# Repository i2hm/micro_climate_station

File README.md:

# Micro Climate Station

PCB designs and firmwares for the Microclimate station.

* [Microclimate station board based on LoRa RAK3172 module](kicad/rak3172_board)
* [Microclimate station board extension for MPPT and PMS7003](kicad/mppt_pms7003_board)
* [868 MHz PCB antenna for LoRa RAK3172 module](kicad/antenna_eu868)
* [Mikrobus adapter for Quectel RTK GNSS LC29H module](kicad/lc29h_mikrobus)

## Licence

[CERN Open Hardware Licence Version 2 - Strongly Reciprocal](./LICENCE.txt) ([wiki](https://ohwr.org/project/cernohl/wikis/home))

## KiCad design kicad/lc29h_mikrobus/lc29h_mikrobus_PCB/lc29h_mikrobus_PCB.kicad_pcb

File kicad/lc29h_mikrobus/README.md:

# Mikrobus click for Quectel LC29H GNSS RTK modules

Designed by Jihane ZEMMOURA with [KiCad EDA](https://www.kicad.org/)

This Mikrobus module is a simplified variant to the [GNSS RTK 3 Click (MIKROE-5914)](https://www.mikroe.com/gnss-rtk-3-click) ([schematic](../../doc/gnss_rtk_3_click/GNSS_RTK_3_Click_v100_Schematic.PDF)).

Its design respects the [Mikrobus form factor](https://download.mikroe.com/documents/standards/mikrobus/mikrobus-standard-specification-v200.pdf). But it is only for 3.3V MCU (ie there is no [voltage regulator](https://product.torexsemi.com/en/system/files/series/xc6209.pdf)). LED are enabled by zero ohm resistors for low-power considerations. The identifier crypto chip ([DS28E36BQ](https://www.maximintegrated.com/en/products/embedded-security/secure-authenticators/DS28C36.html/storefront/my-quotes.html)) is optional.

Thanks to Quectel for supporting us:
* 17 [LC29HEAMD](https://www.quectel.com/product/gnss-lc29h) for rovers
* 8 [LC29HBSAMD](https://www.quectel.com/product/gnss-lc29h) for bases
* 25 [YG0063AA L1/L2/L5 high precision GNSS antennas](https://www.quectel.com/product/yg0063aa-high-precision-gnss-screw-mount-antenna/) + 3m cable TNC-K (F) to SMA(M) , RG174 cable

[Schematic](schematic.pdf)

Configuration tool QGNSS :
* https://market.quectel.com/docsdownload/QGNSS_V1.10_EN.zip
* https://github.com/quectel-open-source/GNSSTool

[Manuals and documents](../../doc/quectel)

## Misc
* [LC29H @ rtklibexplorer](https://rtklibexplorer.wordpress.com/?s=LC29H)
* [TinyGS 2G4 : LoRa 2.4 GHz + GNSS RTK](https://github.com/thingsat/tinygs_2g4station)
* [Integration of LoRa technology and centimeter-level geo-localization by satellites in GNSS/RTK systems](https://journees-lpwan-2023.liglab.fr/Presentations/poster-RTK-LoRa.pdf) (N. Palix, Univ. Grenoble Alpes)
* [LC29H hat for RPI](https://www.waveshare.com/wiki/LC29H(XX)_GPS/RTK_HAT)
* [Pi Click Shield MIKROE-1513](https://www.mikroe.com/pi-click-shield-connectors-soldered) for Raspberry Pi

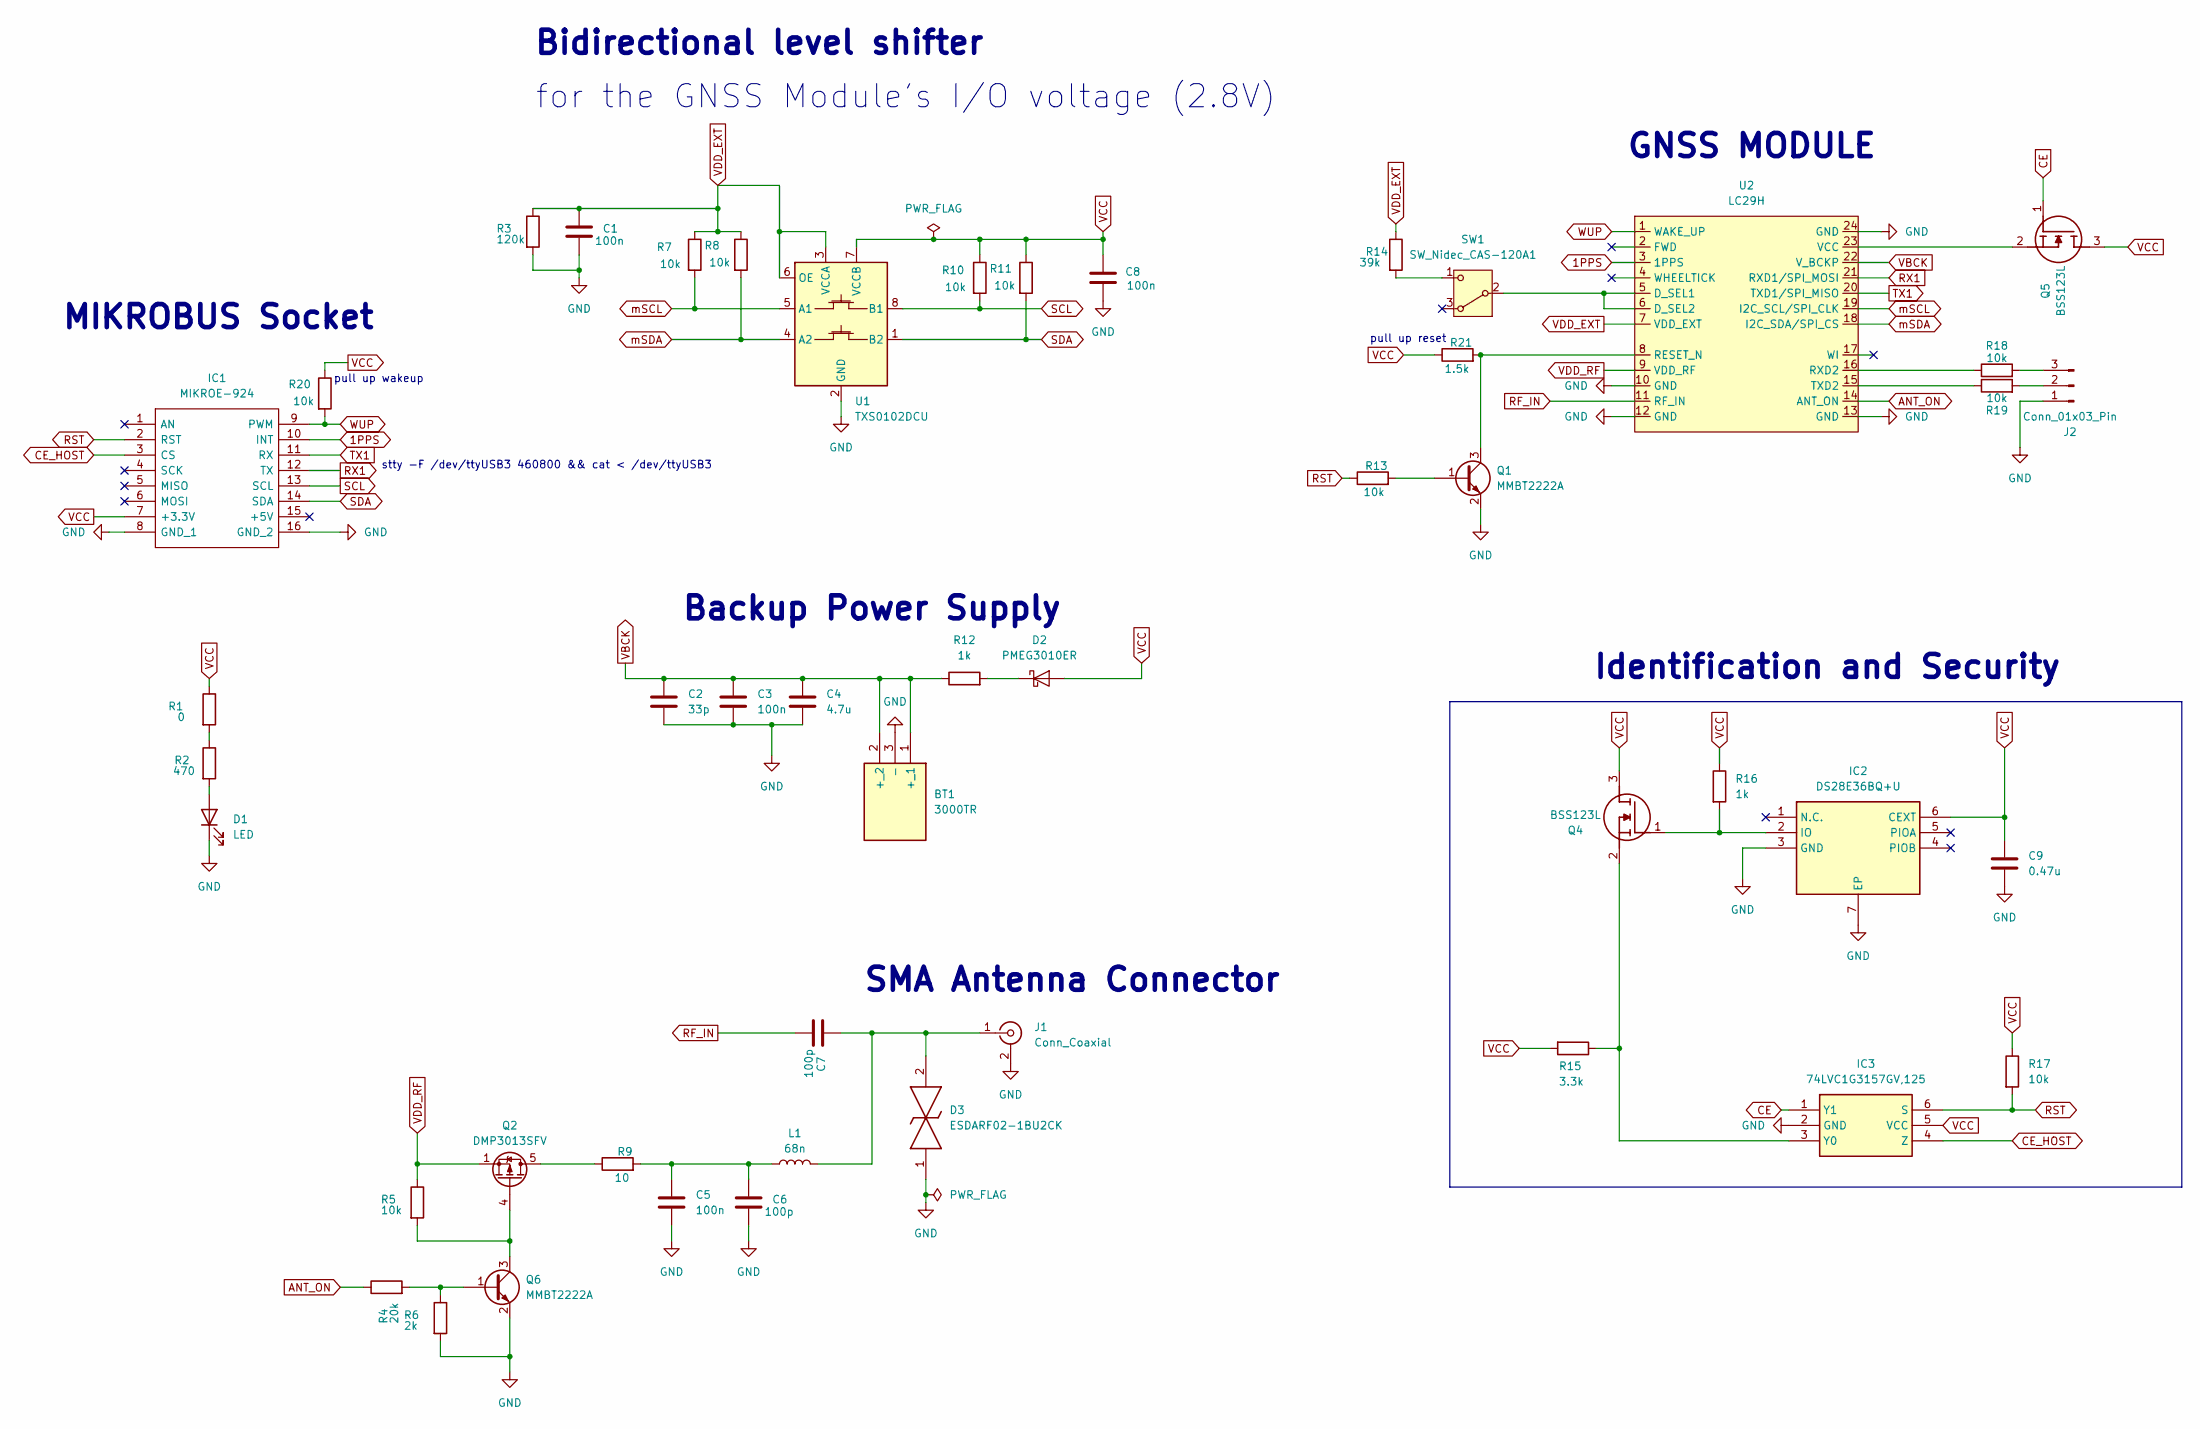
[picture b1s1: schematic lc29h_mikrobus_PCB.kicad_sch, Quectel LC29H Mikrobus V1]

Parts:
BT1: 3000TR; Manufacturer_Part_Number 3000TR; Mouser Part Number 534-3000TR
C1, C3, C5, C8: 100n; C_0805_2012Metric_Pad1.18x1.45mm_HandSolder
C2: 33p; C_0805_2012Metric_Pad1.18x1.45mm_HandSolder
C4: 4.7u; C_0805_2012Metric_Pad1.18x1.45mm_HandSolder
C6, C7: 100p; C_0805_2012Metric_Pad1.18x1.45mm_HandSolder
C9: 0.47u; C_0805_2012Metric_Pad1.18x1.45mm_HandSolder
D1: LED; LED_0402_1005Metric
D2: PMEG3010ER; Nexperia_CFP3_SOD-123W
D3: ESDARF02-1BU2CK; ESDARF021BU2CK; Manufacturer_Part_Number ESDARF02-1BU2CK; Mouser Part Number 511-ESDARF02-1BU2CK
IC1: MIKROE-924; MIKROE924; Manufacturer_Part_Number MIKROE-924; Mouser Part Number 932-MIKROE-924
IC2: DS28E36BQ+U; SON95P300X300X80-7N; Manufacturer_Part_Number DS28E36BQ+U; Mouser Part Number 700-DS28E36BQ+U
IC3: 74LVC1G3157GV,125; SOP95P275X110-6N; Manufacturer_Part_Number 74LVC1G3157GV,125
J1: Conn_Coaxial; SMA_Amphenol_901-144_Vertical
J2: Conn_01x03_Pin; PinHeader_1x03_P1.27mm_Vertical
L1: 68n; L_0805_2012Metric_Pad1.05x1.20mm_HandSolder
Q1, Q6: MMBT2222A; SOT-23
Q2: DMP3013SFV; Diodes_PowerDI3333-8
Q4, Q5: BSS123L; SOT96P237X111-3N; Manufacturer_Part_Number BSS123L; Mouser Part Number 512-BSS123L
R1: 0; R_0603_1608Metric_Pad0.98x0.95mm_HandSolder
R2: 470; R_0805_2012Metric_Pad1.20x1.40mm_HandSolder
R3: 120k; R_0805_2012Metric_Pad1.20x1.40mm_HandSolder
R4: 20k; R_0805_2012Metric_Pad1.20x1.40mm_HandSolder
R5, R7, R8, R10, R11, R13, R17, R18, R19, R20: 10k; R_0805_2012Metric_Pad1.20x1.40mm_HandSolder
R6: 2k; R_0805_2012Metric_Pad1.20x1.40mm_HandSolder
R9: 10; R_0805_2012Metric_Pad1.20x1.40mm_HandSolder
R12, R16: 1k; R_0805_2012Metric_Pad1.20x1.40mm_HandSolder
R14: 39k; R_0805_2012Metric_Pad1.20x1.40mm_HandSolder
R15: 3.3k; R_0805_2012Metric_Pad1.20x1.40mm_HandSolder
R21: 1.5k; R_0805_2012Metric_Pad1.20x1.40mm_HandSolder
SW1: SW_Nidec_CAS-120A1; Nidec_Copal_CAS-120A
U1: TXS0102DCU; VSSOP-8_2.3x2mm_P0.5mm
U2: LC29H; LC29HEA

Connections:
1PPS: IC1.10 (INT), U2.3 (1PPS)
ANT_ON: R4.1, U2.14 (ANT_ON)
CE: IC3.1 (Y1), Q5.1 (G)
CE_HOST: IC1.3 (CS), IC3.4 (Z)
GND: BT1.3 (-), C1.2, C2.2, C3.2, C4.2, C5.2, C6.2, C8.2, C9.2, D1.1 (K), D3.1, IC1.8 (GND_1), IC1.16 (GND_2), IC2.3 (GND), IC2.7 (EP), IC3.2 (GND), J1.2 (Ext), J2.1, Q1.2 (E), Q6.2 (E), R3.2, R6.2, U1.2 (GND), U2.10 (GND), U2.12 (GND), U2.13 (GND), U2.24 (GND)
unnamed: C5.1, C6.1, L1.1, R9.2
unnamed: D1.2 (A), R2.2
unnamed: D2.1 (K), R12.2
unnamed: IC2.2 (IO), Q4.1 (G), R16.2
unnamed: IC3.3 (Y0), Q4.2 (S), R15.1
unnamed: C7.1, D3.2, J1.1 (In), L1.2
unnamed: J2.2, R19.2
unnamed: J2.3, R18.2
unnamed: Q1.1 (B), R13.2
unnamed: Q1.3 (C), R21.2, U2.8 (RESET_N)
unnamed: Q2.5 (D), R9.1
unnamed: Q2.4 (G), Q6.3 (C), R5.2
unnamed: Q5.2 (S), U2.23 (VCC)
unnamed: Q6.1 (B), R4.2, R6.1
unnamed: R1.2, R2.1
unnamed: SW1.2 (B), U2.5 (D_SEL1), U2.6 (D_SEL2)
unnamed: R14.2, SW1.1 (C)
unnamed: R18.1, U2.16 (RXD2)
unnamed: R19.1, U2.15 (TXD2)
RF_IN: C7.2, U2.11 (RF_IN)
RST: IC1.2 (RST), IC3.6 (S), R13.1, R17.2
RX1: IC1.12 (TX), U2.21 (RXD1/SPI_MOSI)
SCL: IC1.13 (SCL), R10.2, U1.8 (B1)
SDA: IC1.14 (SDA), R11.2, U1.1 (B2)
TX1: IC1.11 (RX), U2.20 (TXD1/SPI_MISO)
VBCK: BT1.1 (+_1), BT1.2 (+_2), C2.1, C3.1, C4.1, R12.1, U2.22 (V_BCKP)
VCC: C8.1, C9.1, D2.2 (A), IC1.7 (+3.3V), IC2.6 (CEXT), IC3.5 (VCC), Q4.3 (D), Q5.3 (D), R1.1, R10.1, R11.1, R15.2, R16.1, R17.1, R20.1, R21.1, U1.7 (VCCB)
VDD_EXT: C1.1, R3.1, R7.1, R8.1, R14.1, U1.3 (VCCA), U1.6 (OE), U2.7 (VDD_EXT)
VDD_RF: Q2.1 (S), Q2.2 (S), Q2.3 (S), R5.1, U2.9 (VDD_RF)
WUP: IC1.9 (PWM), R20.2, U2.1 (WAKE_UP)
mSCL: R7.2, U1.5 (A1), U2.19 (I2C_SCL/SPI_CLK)
mSDA: R8.2, U1.4 (A2), U2.18 (I2C_SDA/SPI_CS)

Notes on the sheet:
Identification and Security
Backup Power Supply
SMA Antenna Connector
pull up reset
stty -F /dev/ttyUSB3 460800 && cat < /dev/ttyUSB3
MIKROBUS Socket
GNSS MODULE
Bidirectional level shifter
for the GNSS Module's I/O voltage (2.8V)
pull up wakeup

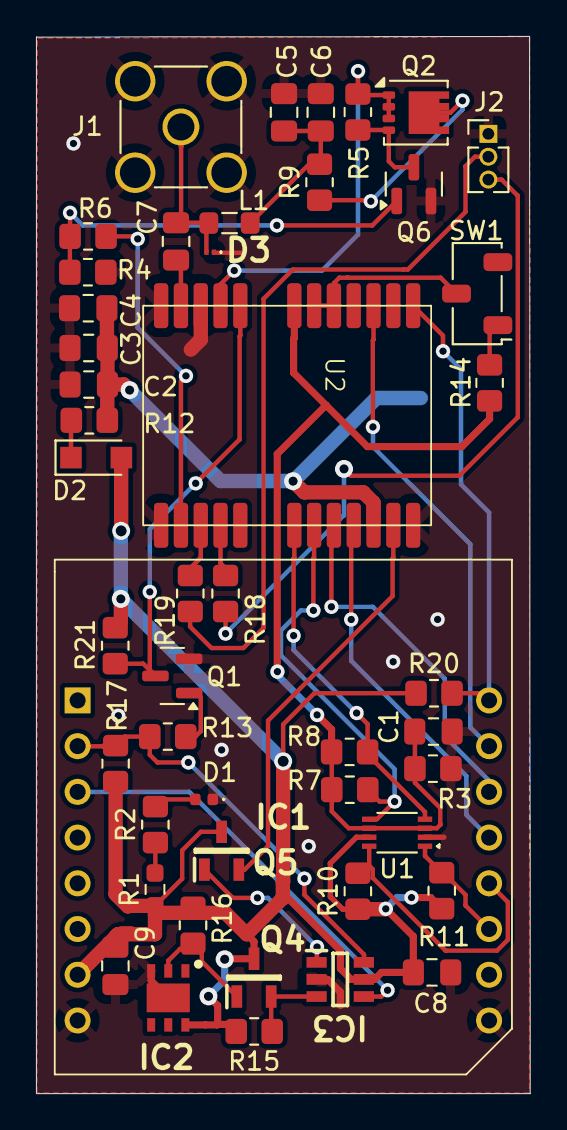
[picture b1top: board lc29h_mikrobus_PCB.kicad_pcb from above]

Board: 2 copper layers, 27.4 x 58.7 mm, 48 parts (1 on the bottom side), 37 nets.

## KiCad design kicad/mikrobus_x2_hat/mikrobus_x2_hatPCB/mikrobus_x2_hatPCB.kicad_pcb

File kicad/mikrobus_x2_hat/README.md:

# Two-slots Mikrobus hat for Raspberry Pi

This hat enables the connection of two Mikrobus click boards to the RPI GPIO header.

## Tested
* [x] [MIKROE-4456 GNSS RTK Click](https://www.mikroe.com/gnss-rtk-click)

## TODO
* [x] fix serigraphy for GPIOs
* [ ] add label and RPI logo in serigraphy
* [ ] add 4 Grove connectors for 1 UART, 1 GPIO and 2 I2C
* [ ] add selector for 3V3 or 5V0 on Grove connectors

## Misc
* https://github.com/devbisme/RPi_Hat_Template
* https://www.mikroe.com/pi-3-click-shield
* https://www.mikroe.com/pi-2-click-shield

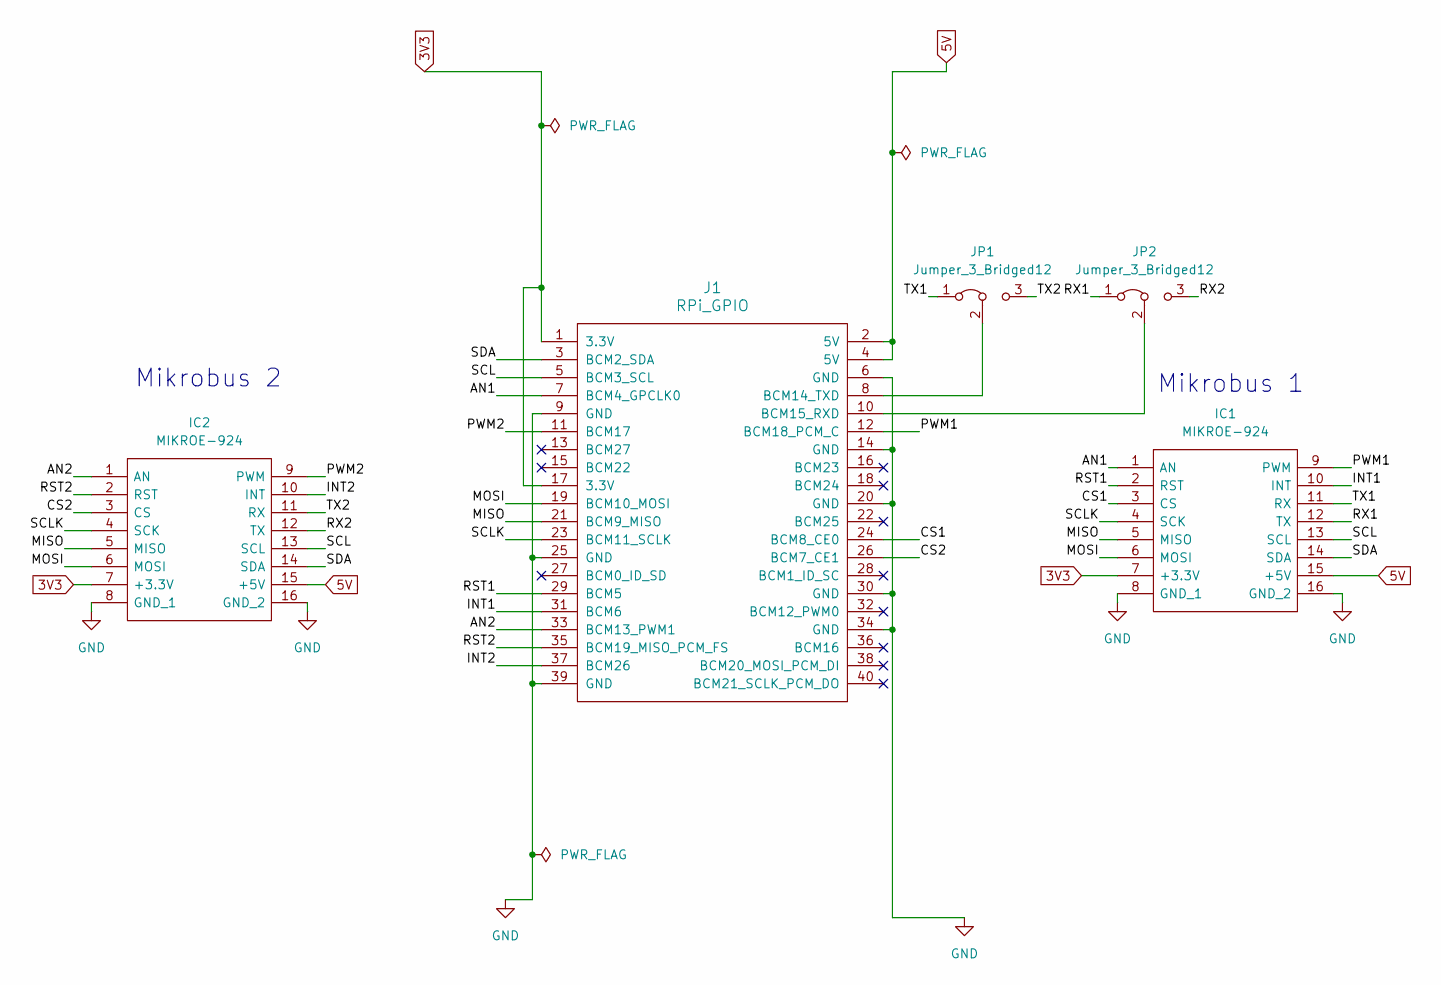
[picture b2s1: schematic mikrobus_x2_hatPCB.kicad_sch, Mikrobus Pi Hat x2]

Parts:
IC1, IC2: MIKROE-924; MIKROE924; Manufacturer_Part_Number MIKROE-924; Mouser Part Number 932-MIKROE-924
J1: RPi_GPIO; PinSocket_2x20_P2.54mm_Vertical
JP1, JP2: Jumper_3_Bridged12; PinHeader_1x03_P2.54mm_Vertical

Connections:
3V3: IC1.7 (+3.3V), IC2.7 (+3.3V), J1.1 (3.3V), J1.17 (3.3V)
5V: IC1.15 (+5V), IC2.15 (+5V), J1.2 (5V), J1.4 (5V)
/AN1: IC1.1 (AN), J1.7 (BCM4_GPCLK0)
/AN2: IC2.1 (AN), J1.33 (BCM13_PWM1)
/CS1: IC1.3 (CS), J1.24 (BCM8_CE0)
/CS2: IC2.3 (CS), J1.26 (BCM7_CE1)
/INT1: IC1.10 (INT), J1.31 (BCM6)
/INT2: IC2.10 (INT), J1.37 (BCM26)
/MISO: IC1.5 (MISO), IC2.5 (MISO), J1.21 (BCM9_MISO)
/MOSI: IC1.6 (MOSI), IC2.6 (MOSI), J1.19 (BCM10_MOSI)
/PWM1: IC1.9 (PWM), J1.12 (BCM18_PCM_C)
/PWM2: IC2.9 (PWM), J1.11 (BCM17)
/RST1: IC1.2 (RST), J1.29 (BCM5)
/RST2: IC2.2 (RST), J1.35 (BCM19_MISO_PCM_FS)
/RX1: IC1.12 (TX), JP2.1 (A)
/RX2: IC2.12 (TX), JP2.3 (B)
/SCL: IC1.13 (SCL), IC2.13 (SCL), J1.5 (BCM3_SCL)
/SCLK: IC1.4 (SCK), IC2.4 (SCK), J1.23 (BCM11_SCLK)
/SDA: IC1.14 (SDA), IC2.14 (SDA), J1.3 (BCM2_SDA)
/TX1: IC1.11 (RX), JP1.1 (A)
/TX2: IC2.11 (RX), JP1.3 (B)
GND: IC1.8 (GND_1), IC1.16 (GND_2), IC2.8 (GND_1), IC2.16 (GND_2), J1.6 (GND), J1.9 (GND), J1.14 (GND), J1.20 (GND), J1.25 (GND), J1.30 (GND), J1.34 (GND), J1.39 (GND)
unnamed: J1.8 (BCM14_TXD), JP1.2 (C)
unnamed: J1.10 (BCM15_RXD), JP2.2 (C)

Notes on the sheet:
Mikrobus 2
Mikrobus 1

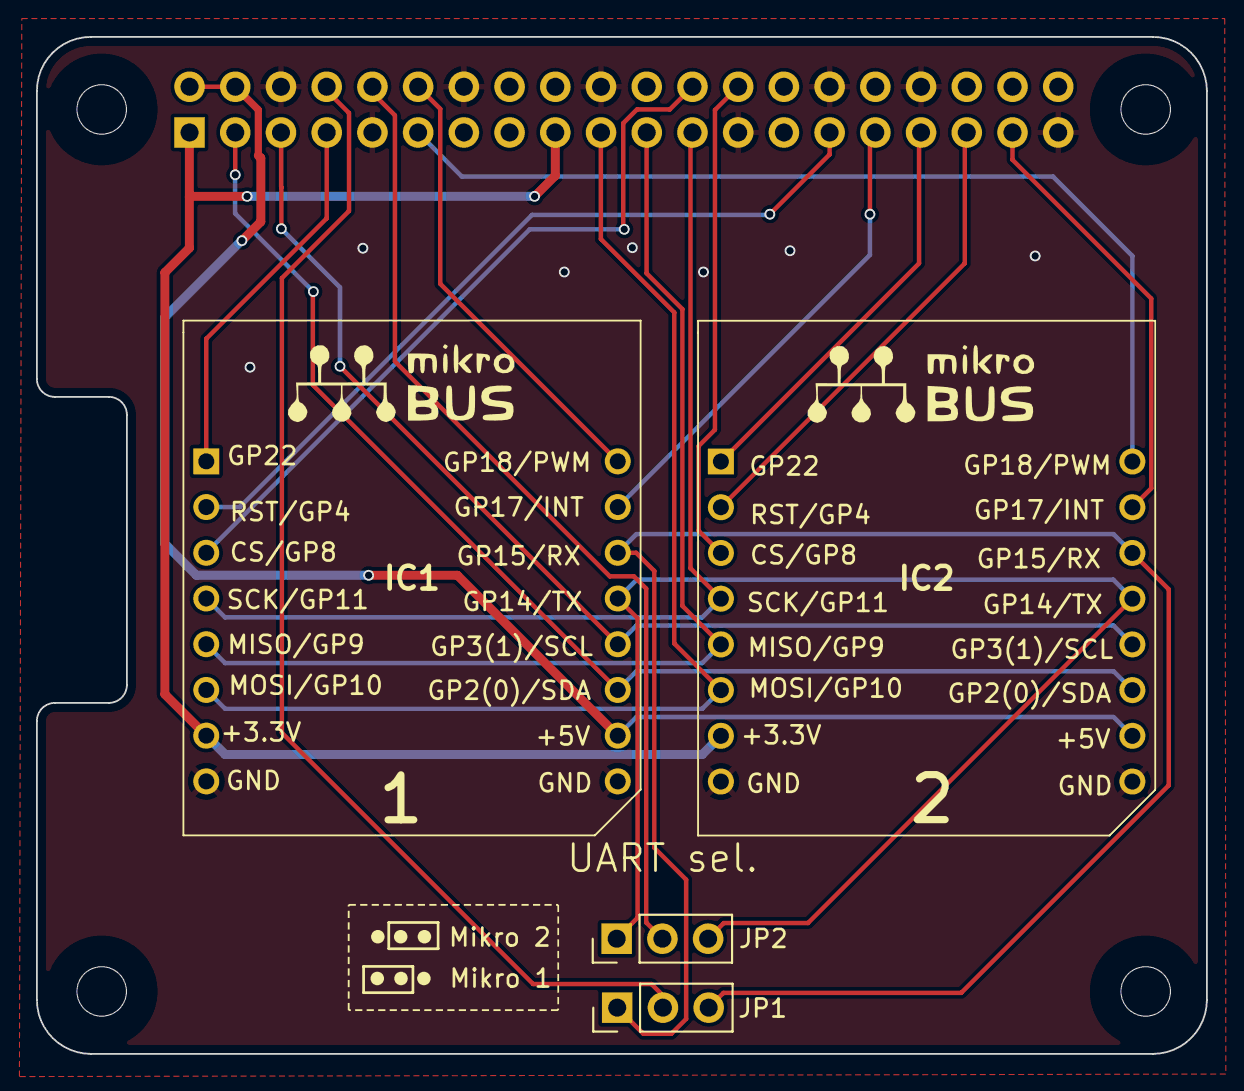
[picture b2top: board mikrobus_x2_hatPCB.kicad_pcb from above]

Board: 2 copper layers, 65.0 x 56.5 mm, 5 parts (1 on the bottom side), 24 nets.

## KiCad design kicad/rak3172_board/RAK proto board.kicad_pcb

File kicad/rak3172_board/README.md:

# I2HM Microclimate Station :: Board (RAK3172 version)

## Features
* [RAK3172](https://store.rakwireless.com/products/wisduo-lpwan-module-rak3172?variant=43329454407878) (MCU [STM32WLE5](https://www.st.com/en/microcontrollers-microprocessors/stm32wlex.html)) LoRa module (available for 800 MHz and 900 MHz regions w/o TCXO)
* On-board Sensors:
  * [BME680](https://www.bosch-sensortec.com/products/environmental-sensors/gas-sensors/bme680/) : Temperature, Humidity, Pressure
  * [LIS2DH12](https://www.st.com/en/mems-and-sensors/lis2dh12.html) : MEMS digital output motion sensor: ultra-low-power high-performance 3-axis "femto" accelerometer
  * [KPS-3227SP1C](https://www.kingbright.com/attachments/file/psearch/000/00/watermark00/KPS-3227SP1C(Ver.9).pdf) ambient light photo sensor
* Grove connectors for UART (x2), I2C (x1), Analog GPIO (x2) and Digital GPIO (x1)  
* Connectivity: LoRaWAN, [LoRa Mesh](https://meshtastic.org/) (coming soon)
* Firmware : [RIOT OS](https://github.com/RIOT-OS/RIOT/tree/master/boards/nucleo-wl55jc), [STM32CubeIDE](https://docs.rakwireless.com/Product-Categories/WisDuo/RAK3172-Module/Low-Level-Development/#rak3172-on-stm32cubeide-with-stm32wl-sdk-v1-2-0)

## HOW TO INSTALL

Clone this repository.

Open the KiCad project using KiCad 7 and above.

If necessary import the symbol and footprint libraries in the project.

## Bonus track

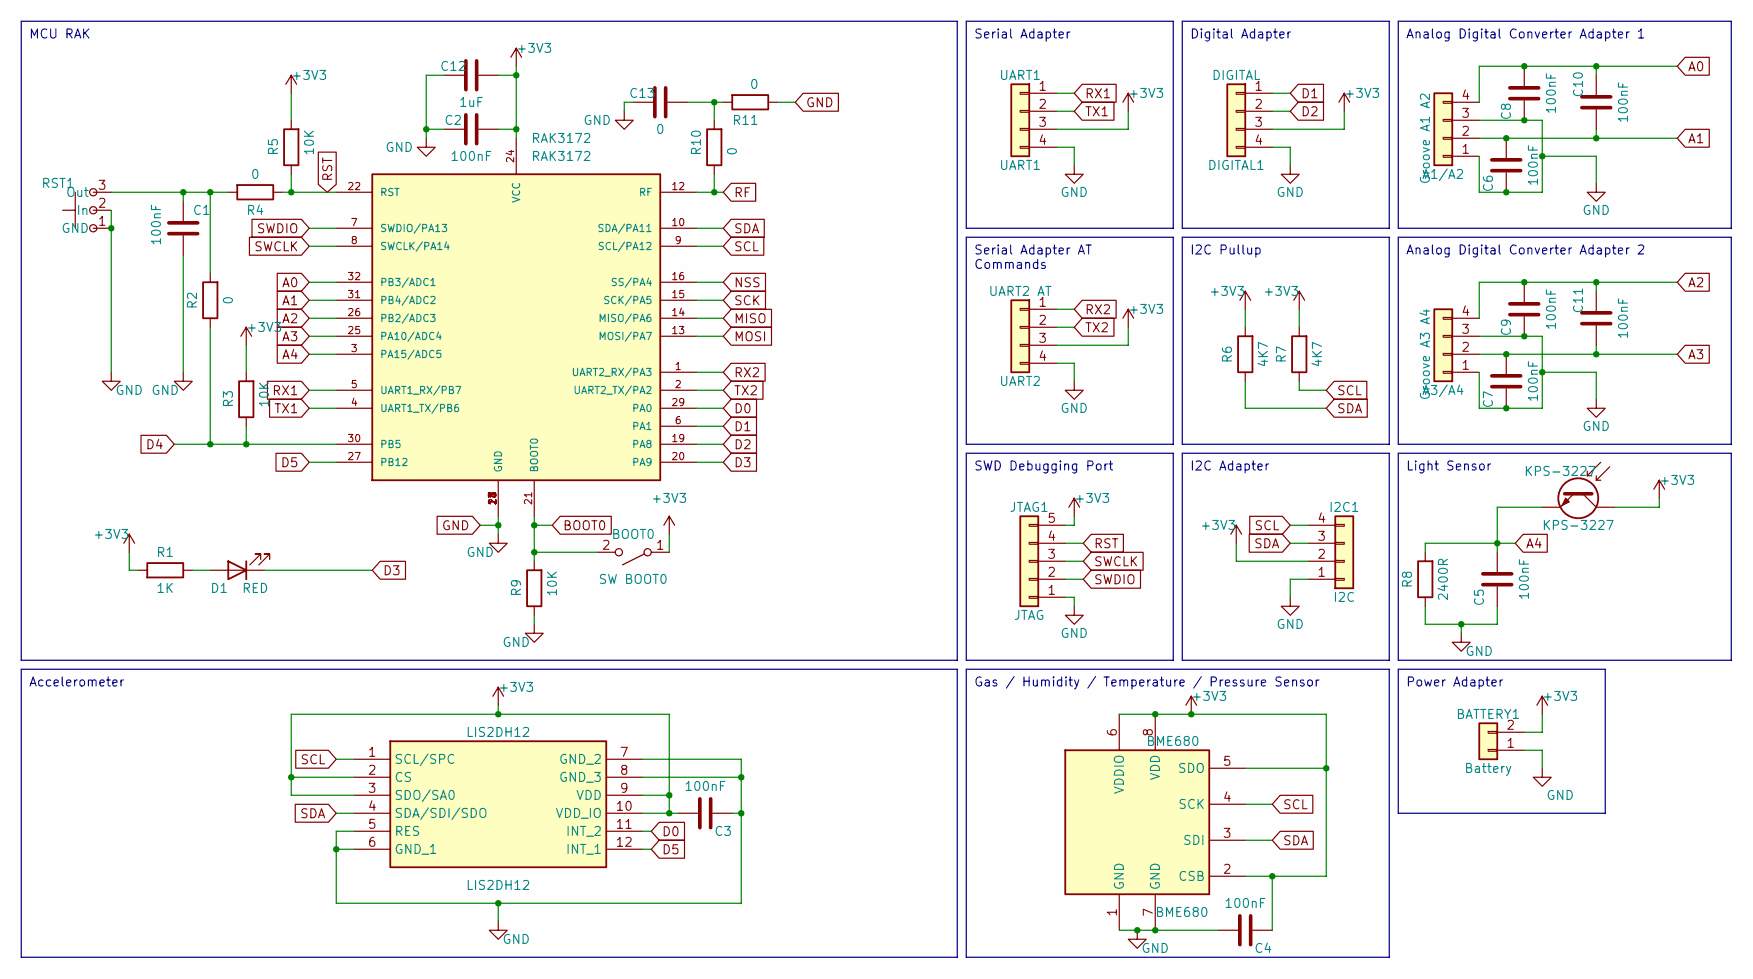
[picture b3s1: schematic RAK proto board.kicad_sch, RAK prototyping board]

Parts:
A1/A2: Groove A1 A2; JST_PH_B4B-PH-K_1x04_P2.00mm_Vertical
A3/A4: Groove A3 A4; JST_PH_B4B-PH-K_1x04_P2.00mm_Vertical
BATTERY1: Battery; PinHeader_1x02_P2.54mm_Horizontal
BME680: BME680; Bosch_LGA-8_3x3mm_P0.8mm_ClockwisePinNumbering
BOOT0: SW BOOT0; SW_Push_1P1T_NO_CK_KMR2
C1, C2, C3, C4, C5, C6, C7, C8, C9, C10, C11: 100nF; CP_EIA-1608-08_AVX-J
C12: 1uF; CP_EIA-1608-08_AVX-J
C13: 0; CP_EIA-1608-08_AVX-J
D1: RED; D_0603_1608Metric
DIGITAL1: DIGITAL; JST_PH_B4B-PH-K_1x04_P2.00mm_Vertical
I2C1: I2C; JST_PH_B4B-PH-K_1x04_P2.00mm_Vertical
JTAG1: JTAG; Conn_JTAG_01x05
KPS-3227: KPS-3227; Kingbright_KPS-3227
LIS2DH12: LIS2DH12; Manufacturer_Part_Number LIS2DH12; Mouser Part Number N/A
R1: 1K; R_0603_1608Metric_Pad0.98x0.95mm_HandSolder
R2, R4, R10, R11: 0; R_0603_1608Metric_Pad0.98x0.95mm_HandSolder
R3, R5, R9: 10K; R_0603_1608Metric_Pad0.98x0.95mm_HandSolder
R6, R7: 4K7; R_0603_1608Metric_Pad0.98x0.95mm_HandSolder
R8: 2400R; R_0603_1608Metric_Pad0.98x0.95mm_HandSolder
RAK3172: RAK3172
RST1: Magnetic_Switch
UART1: UART1; JST_PH_B4B-PH-K_1x04_P2.00mm_Vertical
UART2: UART2 AT; JST_PH_B4B-PH-K_1x04_P2.00mm_Vertical

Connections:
+3V3: BATTERY1.2, BME680.2 (CSB), BME680.5 (SDO), BME680.6 (VDDIO), BME680.8 (VDD), BOOT0.1 (A), C2.2, C3.2, C4.1, C12.2, DIGITAL1.3, I2C1.2, JTAG1.5, KPS-3227.1, KPS-3227.3, LIS2DH12.2 (CS), LIS2DH12.3 (SDO/SA0), LIS2DH12.9 (VDD), LIS2DH12.10 (VDD_IO), R1.2, R3.2, R5.2, R6.2, R7.2, RAK3172.24 (VCC), UART1.3, UART2.3
A0: A1/A2.4, C8.2, C10.2, RAK3172.32 (PB3/ADC1)
A1: A1/A2.2, C6.2, C10.1, RAK3172.31 (PB4/ADC2)
A2: A3/A4.4, C9.2, C11.2, RAK3172.26 (PB2/ADC3)
A3: A3/A4.2, C7.2, C11.1, RAK3172.25 (PA10/ADC4)
A4: C5.2, KPS-3227.2, KPS-3227.4, R8.2, RAK3172.3 (PA15/ADC5)
BOOT0: BOOT0.2 (B), R9.2, RAK3172.21 (BOOT0)
D0: LIS2DH12.11 (INT_2), RAK3172.29 (PA0)
D1: DIGITAL1.1, RAK3172.6 (PA1)
D2: DIGITAL1.2, RAK3172.19 (PA8)
D3: D1.1 (K), RAK3172.20 (PA9)
D4: R2.1, R3.1, RAK3172.30 (PB5)
D5: LIS2DH12.12 (INT_1), RAK3172.27 (PB12)
GND: A1/A2.1, A1/A2.3, A3/A4.1, A3/A4.3, BATTERY1.1, BME680.1 (GND), BME680.7 (GND), C1.2, C2.1, C3.1, C4.2, C5.1, C6.1, C7.1, C8.1, C9.1, C12.1, C13.1, DIGITAL1.4, I2C1.1, JTAG1.1, LIS2DH12.5 (RES), LIS2DH12.6 (GND_1), LIS2DH12.7 (GND_2), LIS2DH12.8 (GND_3), R8.1, R9.1, R11.1, RAK3172.11 (GND), RAK3172.17 (GND), RAK3172.18 (GND), RAK3172.23 (GND), RAK3172.28 (GND), RST1.1 (GND), RST1.2 (In), UART1.4, UART2.4
MISO: RAK3172.14 (MISO/PA6)
MOSI: RAK3172.13 (MOSI/PA7)
NSS: RAK3172.16 (SS/PA4)
unnamed: C13.2, R10.2, R11.2
unnamed: D1.2 (A), R1.1
unnamed: C1.1, R2.2, R4.2, RST1.3 (Out)
RF: R10.1, RAK3172.12 (RF)
RST: JTAG1.4, R4.1, R5.1, RAK3172.22 (RST)
RX1: RAK3172.5 (UART1_RX/PB7), UART1.1
RX2: RAK3172.1 (UART2_RX/PA3), UART2.1
SCK: RAK3172.15 (SCK/PA5)
SCL: BME680.4 (SCK), I2C1.4, LIS2DH12.1 (SCL/SPC), R7.1, RAK3172.9 (SCL/PA12)
SDA: BME680.3 (SDI), I2C1.3, LIS2DH12.4 (SDA/SDI/SDO), R6.1, RAK3172.10 (SDA/PA11)
SWCLK: JTAG1.3, RAK3172.8 (SWCLK/PA14)
SWDIO: JTAG1.2, RAK3172.7 (SWDIO/PA13)
TX1: RAK3172.4 (UART1_TX/PB6), UART1.2
TX2: RAK3172.2 (UART2_TX/PA2), UART2.2

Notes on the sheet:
Analog Digital Converter Adapter 1
I2C Adapter
Serial Adapter AT Commands
Serial Adapter
SWD Debugging Port
I2C Pullup
MCU RAK
Accelerometer
Gas / Humidity / Temperature / Pressure Sensor
Power Adapter
Analog Digital Converter Adapter 2
Digital Adapter
Light Sensor

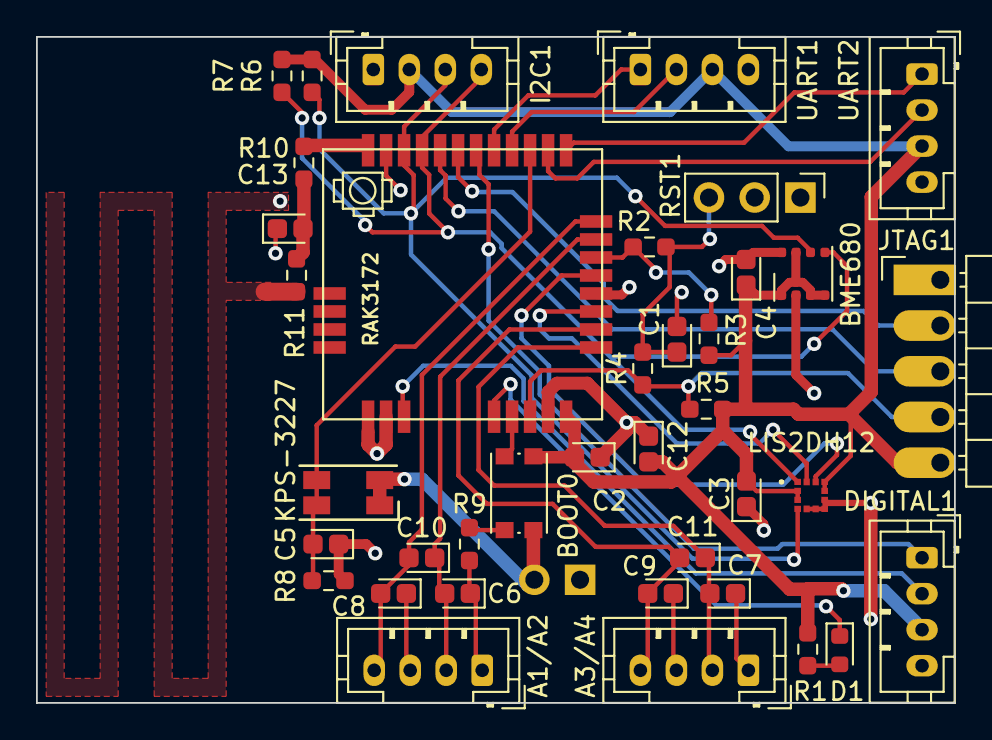
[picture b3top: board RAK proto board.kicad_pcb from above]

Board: 2 copper layers, 51.0 x 37.0 mm, 39 parts (1 on the bottom side), 27 nets.

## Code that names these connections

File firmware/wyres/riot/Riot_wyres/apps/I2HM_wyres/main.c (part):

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		  .sensor0_pin = GPIO_PIN(PORT_B, 14), //PB14, Port MISO en bas de la carte 
		  .sensor0_mode = GPIO_IN, 
          // anémomètre 
		  .sensor1_pin = EXTERNAL_GPIO_PIN, // PA8, en bas à droite de la carte
		  .sensor1_mode = GPIO_IN_PD, 
		  .sensor1_flank = GPIO_RISING, 
		 // Pluviomètre
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        puts("LORAMAC buffer sent");
        // clear GPIO for consumption ( not efficient for the moment) 
        /*
        gpio_clear(LED_RED_PIN);                // PA15 
        gpio_clear(LED_GREEN_PIN);              // PA0 
        gpio_clear(LIGHT_SENSOR_SUPPLY_PIN);    // PB6 
        gpio_clear(BTN1_PIN);                   // PB3 
        gpio_clear(SX127X_PARAM_SPI_NSS );      //SPI1_CS 
        gpio_set(SX127X_PARAM_RESET);
        gpio_clear(SX127X_PARAM_RESET);         // PA2 
        gpio_clear(SX127X_PARAM_DIO0);          // PA10 
        gpio_clear(SX127X_PARAM_DIO1);          // PB10 
        gpio_clear(SX127X_PARAM_DIO2);          // PB11 
        gpio_clear(SX127X_PARAM_DIO3);          // PB7 
        gpio_clear(SX127X_PARAM_DIO4) ;         // PB5 
        gpio_clear(SX127X_PARAM_DIO5) ;         // PB4 
        */
        puts("LORAMAC start waiting");
        LED_RED_OFF;
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
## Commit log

2024-01-30 create repo
2024-01-30 add layout
2024-01-30 add dir for doc
2024-01-31 add dirs for firmwares
2024-02-06 add dir for Kicad projects
2024-02-08 new dir for antenna design
2024-02-08 Added KiCad project
2024-02-09 improve readme
2024-02-13 Updated schematic and pcb
2024-02-22 Ordered v1.0 on JLCPCB
2024-02-24 add contributors
2024-02-24 fix name
2024-02-24 add readme
2024-02-24 add doc
2024-02-24 add ref to mikrobus spec
2024-02-24 add doc for gnss_rtk_3_click
2024-02-24 add ref to schematic
2024-02-24 update gitignore
2024-02-24 add remarks
2024-02-24 add organizations
2024-02-24 add images
2024-02-24 fix paths
2024-02-25 fix filename
2024-02-25 add extension board
2024-03-13 RAK3172/RAK3272S
    Documents et code liés à l'utilisation de la devboard RAK3272S implémentant la carte RAK3172.
2024-03-13 Add I2HM wyres riot project
2024-03-15 add github id
2024-03-27 add licence
2024-03-27 fix titles
2024-03-27 change title
2024-03-27 add features
2024-03-27 fix 900 MHz region
2024-03-27 remove PMS
2024-03-27 add KPS-3227SP1C$
2024-03-27 add image
2024-03-27 add ads1115
2024-03-27 move image
2024-04-09 init flipper_zero_mikrobus
2024-04-23 add ref
2024-05-12 refactor layout for ino
2024-05-12 add install for Arduino IDE
2024-05-12 add ref to boards
2024-07-02 initialisation de la carte PCB
2024-07-02 Ajout symboles/empreintes composants
2024-07-02 Début circuit
2024-07-03 ajout level shifter pour le module GNSS
2024-07-03 ajout bibliothèque LC29H
2024-07-04 schematic module gnss, clickID et voltage translator
2024-07-04 Positionnement des composants dans RTK_CLICK
2024-07-04 signaux ant_on, rf_in, vdd_rf
2024-07-04 Ajout empreinte PCB
2024-07-04 connecteur 3broches+ batterie
2024-07-04 batterie+connecteur3Broches
2024-07-05 debut connexion pcb
2024-07-05 Connexion PCB Composant et alimentation
2024-07-05 association de toutes les empreintes et début de la finalisation du routage
2024-07-08 routage carte terminé
2024-07-09 add attributes
2024-07-09 add schematic
2024-07-10 remove backup from git repo
2024-07-10 add gitignore
2024-07-10 fix ref to image
2024-07-10 add author
2024-07-11 assign proper power pin to remove ERC errors in schematic
2024-07-11 typo
2024-07-11 add power symbols and update schematic to remove all errors and warnings
2024-07-11 replace explicit ground routing with ground plane
2024-07-11 remove all errors in Design Rule Check
2024-07-11 update schematic
2024-07-11 add misc
2024-07-12 rearrange components and remove most warnings
2024-07-13 add ref to RPI hat
2024-07-13 add url
2024-07-13 init mikrobus hats
2024-07-13 init mikrobus_protoboard
2024-07-13 apply gitignore to all kicad projects
2024-07-15 Update README.md
    (No level shifter -> No voltage regulator) The level shifter is needed to ensure communication with the GNSS module while the regulator( 5V->3V3) must be removed.
2024-07-15 BSS123L connections corrected and schematic commented
2024-07-15 add power flag and NC to remove errors in schematic ERC
2024-07-16 0 ERC errors/warnings after editing symbols
2024-07-16 Project creation
2024-07-16 updating libraries
2024-07-18 schematic complete with 0 ERC errors
2024-07-18 Kicad project creation
2024-07-18 Adding card borders
2024-07-22 nets complete
2024-07-22 pcb routing initiated
2024-07-24 Component footprints
2024-07-29 protoboard ready
2024-07-29 PCB completed
2024-07-30 MikroBUS logo added
2024-07-30 init projet
2024-07-30 ajout gerber
2024-07-30 adding pin texts and logos
2024-07-30 update protoboard gerber
2024-07-30 update mikrobus_x1 gerber
2024-07-30 update mikrobus_x2 gerber
2024-07-30 update mikrobus protoboard gerber
2024-07-30 update lc29h gerber
2024-07-30 mass layer isolation adjusted
2024-07-31 add power and gnd
2024-09-02 init mikrobus_groove pcb
2024-09-02 add todo
2024-09-03 init new PCBs
2024-09-03 init new PCB for I2C EEPROM
2024-09-03 fix serigraphy
2024-09-03 invert RX TX
2024-09-03 add ref to kicad design
2024-09-09 add description
2024-09-09 init new shield projects
2024-09-10 add usage section
2024-09-19 add PDF of schematic
2024-09-20 add examples for ADS
2024-09-20 init board for tracking
2024-09-21 add ref to lib
2024-09-21 add ref to e-peas
2024-09-21 add lithium-ion capa
2024-10-15 reprise schematique, clarification
2024-10-15 debut routage
2024-10-16 final commit
2024-11-14 add datasheet
2024-11-28 replace all 201 SMD components with 805 for hand soldering
2024-11-28 pull up resistors and remove silkscreen warnings
2025-01-09 add mikrobus_mpl3115a2
2025-01-12 init grove_mpl3115a2
2025-03-02 init readme
2025-03-02 add toc
2025-03-02 move ref for upper level
2025-03-02 move refs to products
2025-03-02 move refs (part 2)
2025-04-05 improve spec for mikrobus nucleo
2025-04-05 add openlog
2025-04-05 add ref to spec
2025-04-05 add ref to grove
2025-04-15 add CC1110

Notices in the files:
firmware/wyres/riot/Riot_wyres/apps/I2HM_wyres/main.c:
Copyright (C) 2024 Université Grenoble Alpes
General Public License v2.1. See the file LICENSE in the top level
kicad/lc29h_mikrobus/lc29h_mikrobus_PCB/lc29h_mikrobus_PCB.kicad_pcb:
(c) 2024 - Université Grenoble Alpes - Grenoble INP - LIG + CSUG
